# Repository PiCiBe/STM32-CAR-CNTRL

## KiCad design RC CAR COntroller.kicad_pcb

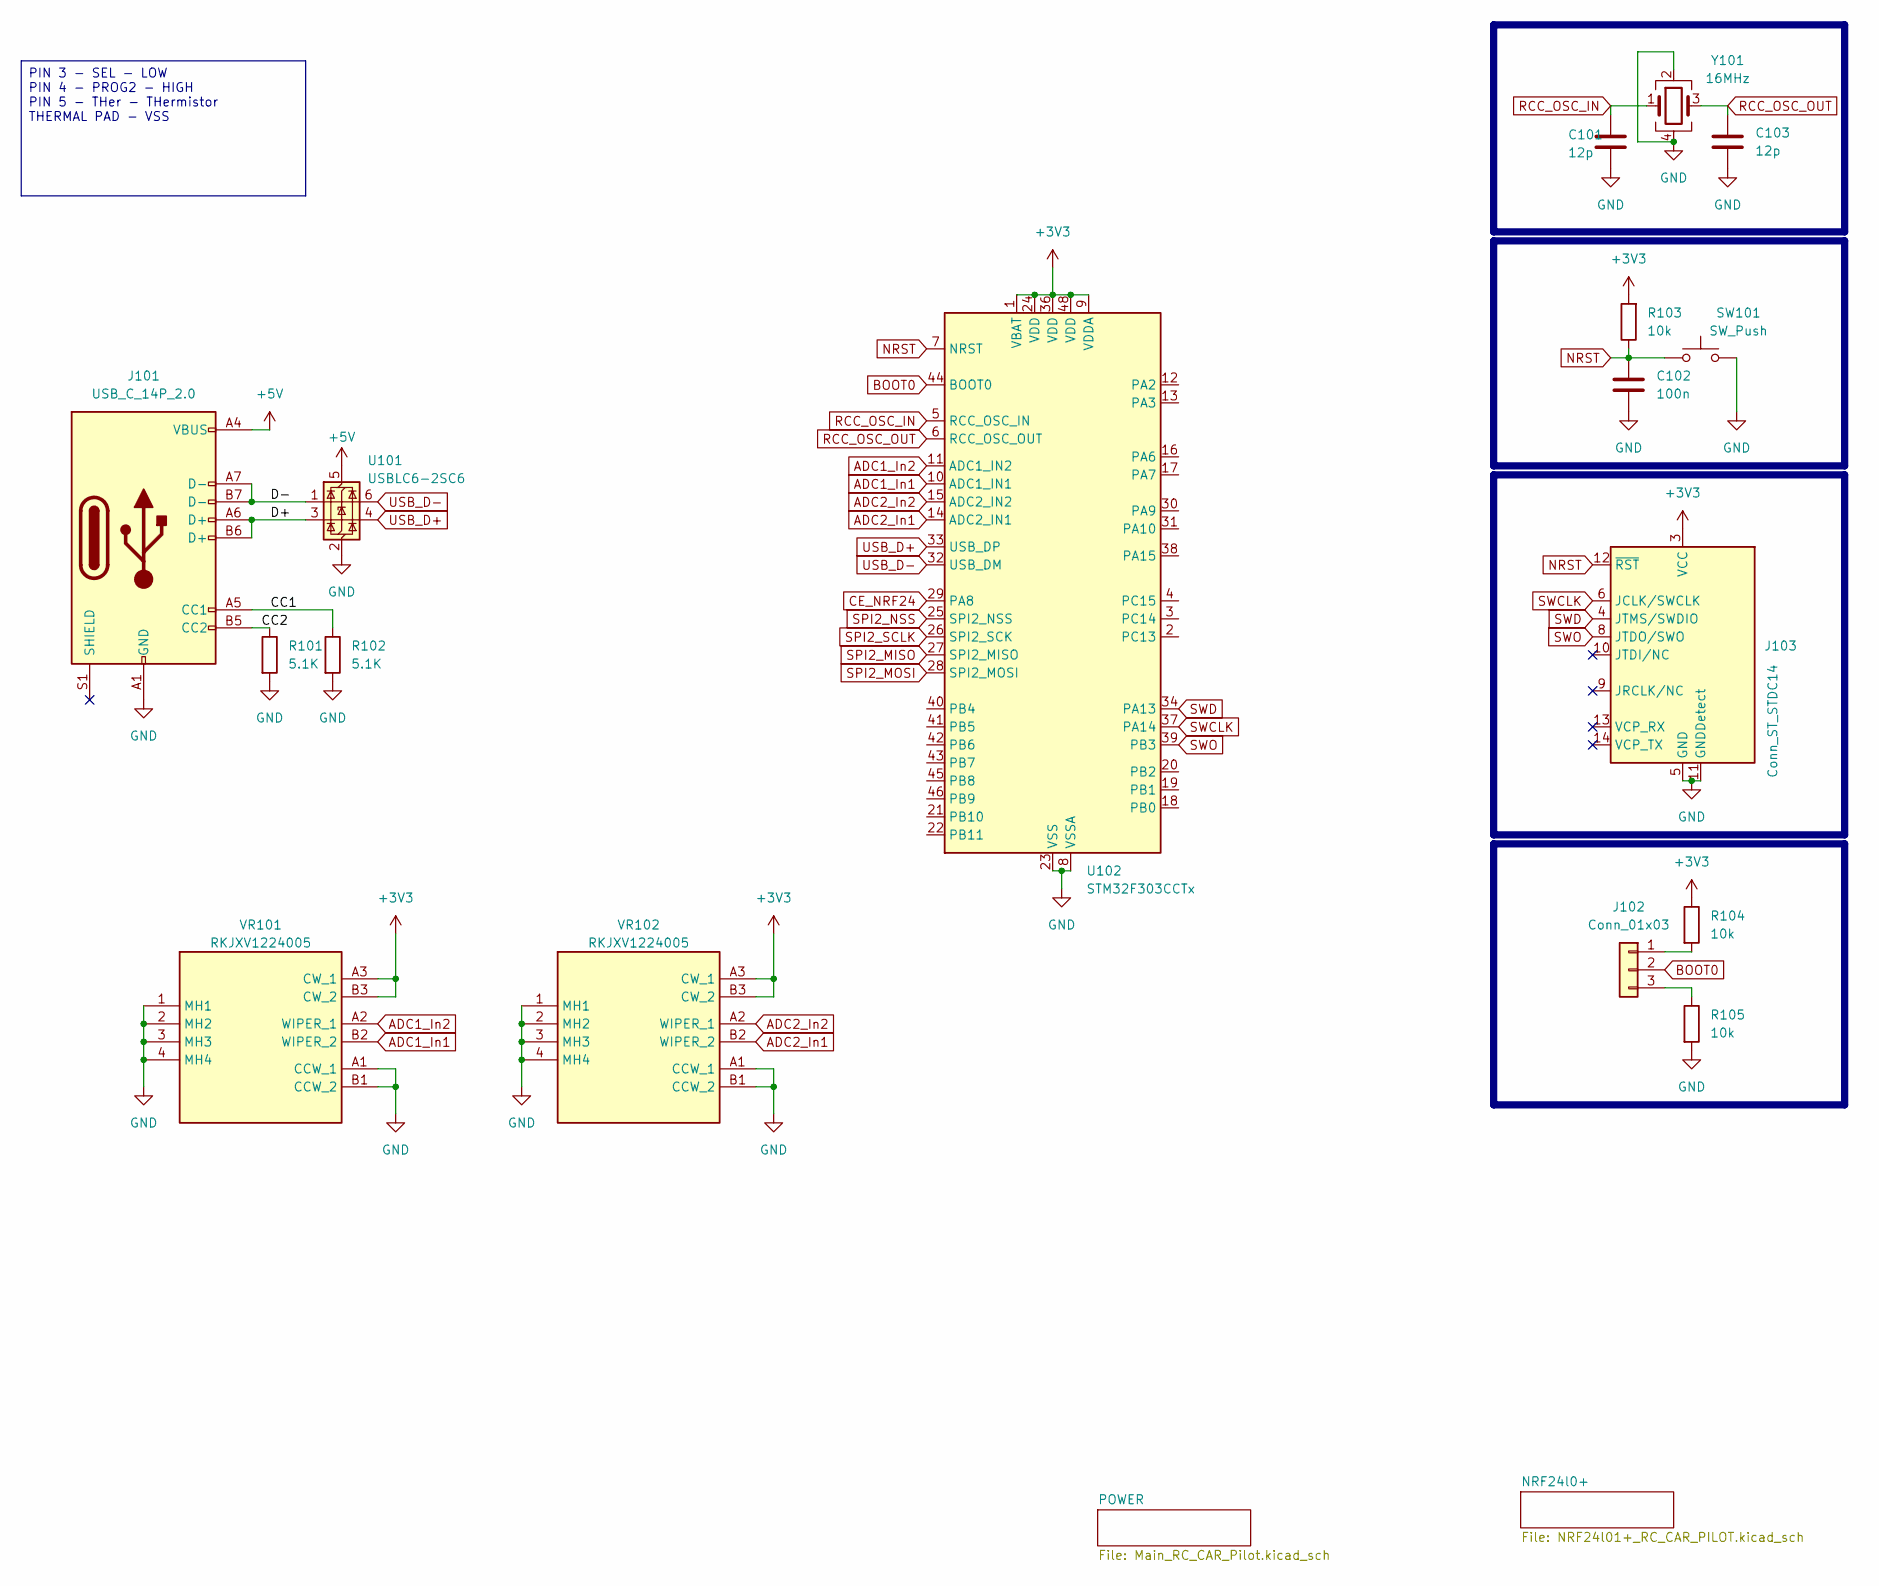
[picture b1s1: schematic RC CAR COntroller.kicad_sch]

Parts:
C101: 12p; C_0402_1005Metric_Pad0.74x0.62mm_HandSolder; lcsc C326662
C102: 100n; C_0603_1608Metric; LCSC C14663
C103: 12p; C_0402_1005Metric_Pad0.74x0.62mm_HandSolder; LCSC C326662
J101: USB_C_14P_2.0; USB_C_Receptacle_G-Switch_GT-USB-7010ASV
J102: Conn_01x03; PinHeader_1x03_P2.54mm_Vertical_SMD_Pin1Left; LCSC C19192025
J103: Conn_ST_STDC14; PinHeader_2x07_P1.27mm_Vertical_SMD
R101, R102: 5.1K; R_0603_1608Metric; LCSC C2907044
R103: 10k; R_0603_1608Metric; lcsc C98220
R104, R105: 10k; R_0603_1608Metric; LCSC C98220
SW101: SW_Push; SW_PUSH_6mm
U101: USBLC6-2SC6; SOT-23-6; LCSC C81523
U102: STM32F303CCTx; LQFP-48_7x7mm_P0.5mm
VR101, VR102: RKJXV1224005; Manufacturer_Part_Number RKJXV1224005; Mouser Part Number 688-RKJXV1224005
Y101: 16MHz; TSX3225160000MF18XAC0; LCSC C1986974

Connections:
+3V3: J103.3 (VCC), R103.2, R104.1, U102.1 (VBAT), U102.9 (VDDA), U102.24 (VDD), U102.36 (VDD), U102.48 (VDD), VR101.A3 (CW_1), VR101.B3 (CW_2), VR102.A3 (CW_1), VR102.B3 (CW_2); also elsewhere on the board
+5V: J101.A4 (VBUS), J101.A9 (VBUS), J101.B4 (VBUS), J101.B9 (VBUS), U101.5 (VBUS); also elsewhere on the board
/D+: J101.A6 (D+), J101.B6 (D+), U101.3 (I/O2)
/D-: J101.A7 (D-), J101.B7 (D-), U101.1 (I/O1)
ADC1_In1: U102.10 (ADC1_IN1), VR101.B2 (WIPER_2)
ADC1_In2: U102.11 (ADC1_IN2), VR101.A2 (WIPER_1)
ADC2_In1: U102.14 (ADC2_IN1), VR102.B2 (WIPER_2)
ADC2_In2: U102.15 (ADC2_IN2), VR102.A2 (WIPER_1)
BOOT0: J102.2, U102.44 (BOOT0)
CE_NRF24: U102.29 (PA8); also elsewhere on the board
GND: C101.2, C102.2, C103.2, J101.A1 (GND), J101.A12 (GND), J101.B1 (GND), J101.B12 (GND), J103.5 (GND), J103.7 (GND), J103.11 (GNDDetect), R101.2, R102.2, R105.2, SW101.2, U101.2 (GND), U102.8 (VSSA), U102.23 (VSS), U102.35 (VSS), U102.47 (VSS), VR101.1 (MH1), VR101.2 (MH2), VR101.3 (MH3), VR101.4 (MH4), VR101.A1 (CCW_1), VR101.B1 (CCW_2), VR102.1 (MH1), VR102.2 (MH2), VR102.3 (MH3), VR102.4 (MH4), VR102.A1 (CCW_1), VR102.B1 (CCW_2), Y101.2, Y101.4; also elsewhere on the board
NRST: C102.1, J103.12 (~RST), R103.1, SW101.1, U102.7 (NRST)
unnamed: J101.A5 (CC1), R102.1
unnamed: J101.B5 (CC2), R101.1
unnamed: J102.1, R104.2
unnamed: J102.3, R105.1
RCC_OSC_IN: C101.1, U102.5 (RCC_OSC_IN), Y101.1
RCC_OSC_OUT: C103.1, U102.6 (RCC_OSC_OUT), Y101.3
SPI2_MISO: U102.27 (SPI2_MISO); also elsewhere on the board
SPI2_MOSI: U102.28 (SPI2_MOSI); also elsewhere on the board
SPI2_NSS: U102.25 (SPI2_NSS); also elsewhere on the board
SPI2_SCLK: U102.26 (SPI2_SCK); also elsewhere on the board
SWCLK: J103.6 (JCLK/SWCLK), U102.37 (PA14)
SWD: J103.4 (JTMS/SWDIO), U102.34 (PA13)
SWO: J103.8 (JTDO/SWO), U102.39 (PB3)
USB_D+: U101.4 (I/O2), U102.33 (USB_DP)
USB_D-: U101.6 (I/O1), U102.32 (USB_DM)

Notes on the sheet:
PIN 3 - SEL - LOW PIN 4 - PROG2 - HIGH PIN 5 - THer - THermistor THERMAL PAD - VSS

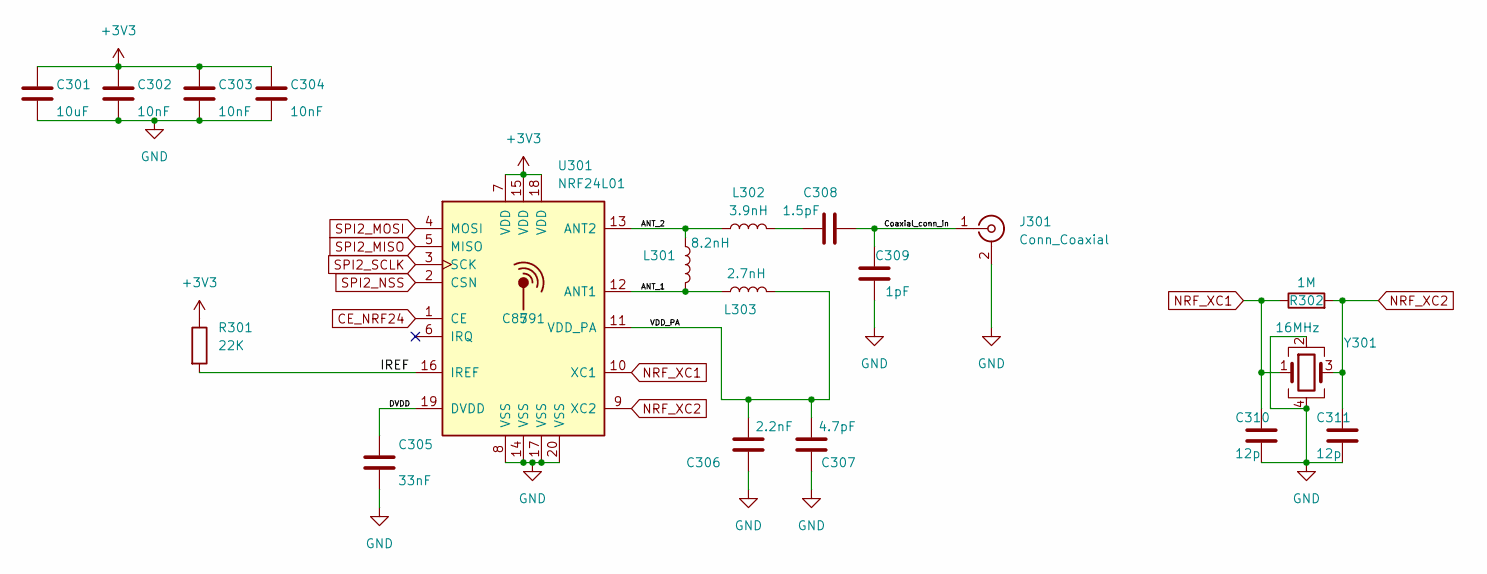
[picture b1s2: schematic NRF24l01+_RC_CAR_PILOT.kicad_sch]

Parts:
C301: 10uF; C_0603_1608Metric_Pad1.08x0.95mm_HandSolder; LCSC C2959727
C302: 10nF; C_0402_1005Metric_Pad0.74x0.62mm_HandSolder; LCSC C60133
C303, C304: 10nF; C_0402_1005Metric_Pad0.74x0.62mm_HandSolder; LCSC part number C60133
C305: 33nF; C_0402_1005Metric_Pad0.74x0.62mm_HandSolder; LCSC C301939
C306: 2.2nF; C_0402_1005Metric_Pad0.74x0.62mm_HandSolder; LCSC C7393866
C307: 4.7pF; C_0402_1005Metric_Pad0.74x0.62mm_HandSolder; LCSC C2915773
C308: 1.5pF; C_0402_1005Metric_Pad0.74x0.62mm_HandSolder; LCSC C189471
C309: 1pF; C_0402_1005Metric_Pad0.74x0.62mm_HandSolder; LCSC C309455
C310: 12p; C_0402_1005Metric_Pad0.74x0.62mm_HandSolder; LCSC C1547
C311: 12p; C_0402_1005Metric_Pad0.74x0.62mm_HandSolder; LCSC part number C1547
J301: Conn_Coaxial; SMA_Amphenol_132134-11_Vertical; LCSC C496550
L301: 8.2nH; L_0402_1005Metric; LCSC C7427065
L302: 3.9nH; L_0402_1005Metric; LCSC C6807988
L303: 2.7nH; L_0402_1005Metric; LCSC C434826
R301: 22K; R_0402_1005Metric_Pad0.72x0.64mm_HandSolder; LCSC C82868
R302: 1M; R_0402_1005Metric_Pad0.72x0.64mm_HandSolder; LCSC C93949
U301: NRF24L01; QFN-20-1EP_4x4mm_P0.5mm_EP2.5x2.5mm; LCSC C8791
Y301: 16MHz; Crystal_SMD_3225-4Pin_3.2x2.5mm; LCSC C13738

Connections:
+3V3: C301.1, C302.1, C303.1, C304.1, R301.1, U301.7 (VDD), U301.15 (VDD), U301.18 (VDD); also elsewhere on the board
/NRF24l0+/ANT_1: L301.1, L303.2, U301.12 (ANT1)
/NRF24l0+/ANT_2: L301.2, L302.1, U301.13 (ANT2)
/NRF24l0+/Coaxial_conn_in: C308.2, C309.2, J301.1 (In)
/NRF24l0+/DVDD: C305.1, U301.19 (DVDD)
/NRF24l0+/VDD_PA: C306.2, C307.2, L303.1, U301.11 (VDD_PA)
CE_NRF24: U301.1 (CE); also elsewhere on the board
GND: C301.2, C302.2, C303.2, C304.2, C305.2, C306.1, C307.1, C309.1, C310.2, C311.2, J301.2 (Ext), U301.8 (VSS), U301.14 (VSS), U301.17 (VSS), U301.20 (VSS), Y301.2, Y301.4; also elsewhere on the board
NRF_XC1: C310.1, R302.1, U301.10 (XC1), Y301.1
NRF_XC2: C311.1, R302.2, U301.9 (XC2), Y301.3
unnamed: C308.1, L302.2
unnamed: R301.2, U301.16 (IREF)
SPI2_MISO: U301.5 (MISO); also elsewhere on the board
SPI2_MOSI: U301.4 (MOSI); also elsewhere on the board
SPI2_NSS: U301.2 (CSN); also elsewhere on the board
SPI2_SCLK: U301.3 (SCK); also elsewhere on the board

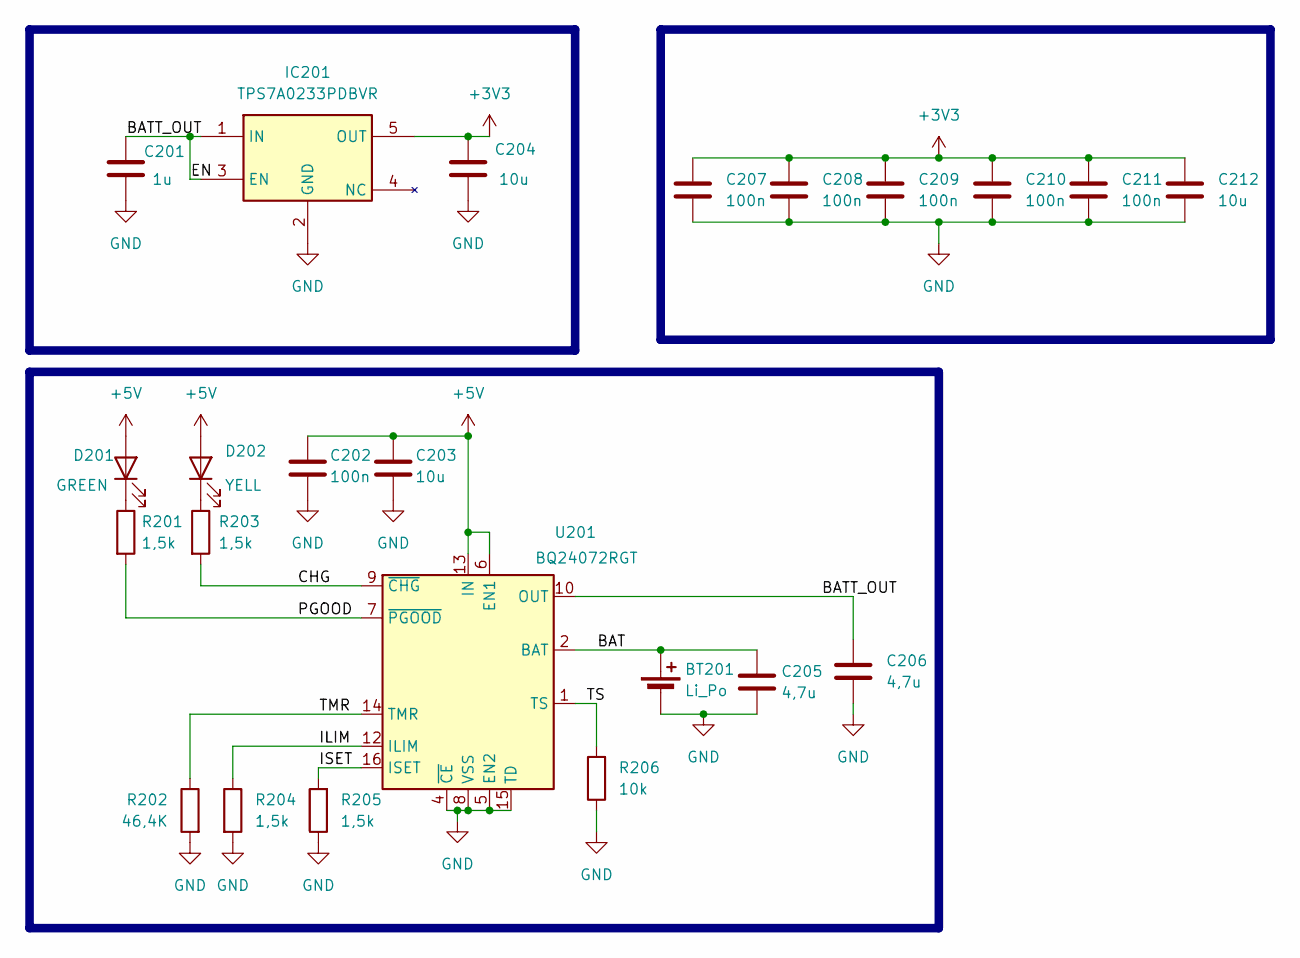
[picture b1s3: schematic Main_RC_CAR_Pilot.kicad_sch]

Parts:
BT201: Li_Po; 532610271; LCSC C177225
C201: 1u; C_0805_2012Metric; lcsc C28323
C202, C207, C208, C209, C210, C211: 100n; C_0603_1608Metric; lcsc C14663
C203, C204, C212: 10u; C_0805_2012Metric; LCSC C15850
C205, C206: 4,7u; C_0805_2012Metric; LCSC C98192
D201: GREEN; LED_0603_1608Metric; LCSC C19171301
D202: YELL; LED_0603_1608Metric; LCSC C965800
IC201: TPS7A0233PDBVR; SOT95P280X145-5N; Manufacturer_Part_Number TPS7A0233PDBVR; Mouser Part Number 595-TPS7A0233PDBVR
R201, R203, R204, R205: 1,5k; R_0603_1608Metric; LCSC C22843
R202: 46,4K; R_0603_1608Metric; LCSC C3013203
R206: 10k; R_0603_1608Metric; LCSC C98220
U201: BQ24072RGT; VQFN-16-1EP_3x3mm_P0.5mm_EP1.6x1.6mm; LCSC C140288

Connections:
+3V3: C204.1, C207.1, C208.1, C209.1, C210.1, C211.1, C212.1, IC201.5 (OUT); also elsewhere on the board
+5V: C202.1, C203.1, D201.2 (A), D202.2 (A), U201.6 (EN1), U201.13 (IN); also elsewhere on the board
/POWER/BAT: BT201.1 (+), C205.1, U201.2 (BAT), U201.3 (BAT)
/POWER/BATT_OUT: C201.1, C206.1, IC201.1 (IN), IC201.3 (EN), U201.10 (OUT), U201.11 (OUT)
/POWER/CHG: R203.2, U201.9 (~CHG)
/POWER/ILIM: R204.1, U201.12 (ILIM)
/POWER/ISET: R205.2, U201.16 (ISET)
/POWER/PGOOD: R201.2, U201.7 (~PGOOD)
/POWER/TMR: R202.1, U201.14 (TMR)
/POWER/TS: R206.2, U201.1 (TS)
GND: BT201.2 (-), C201.2, C202.2, C203.2, C204.2, C205.2, C206.2, C207.2, C208.2, C209.2, C210.2, C211.2, C212.2, IC201.2 (GND), R202.2, R204.2, R205.1, R206.1, U201.4 (~CE), U201.5 (EN2), U201.8 (VSS), U201.15 (TD), U201.17 (VSS); also elsewhere on the board
unnamed: D201.1 (K), R201.1
unnamed: D202.1 (K), R203.1

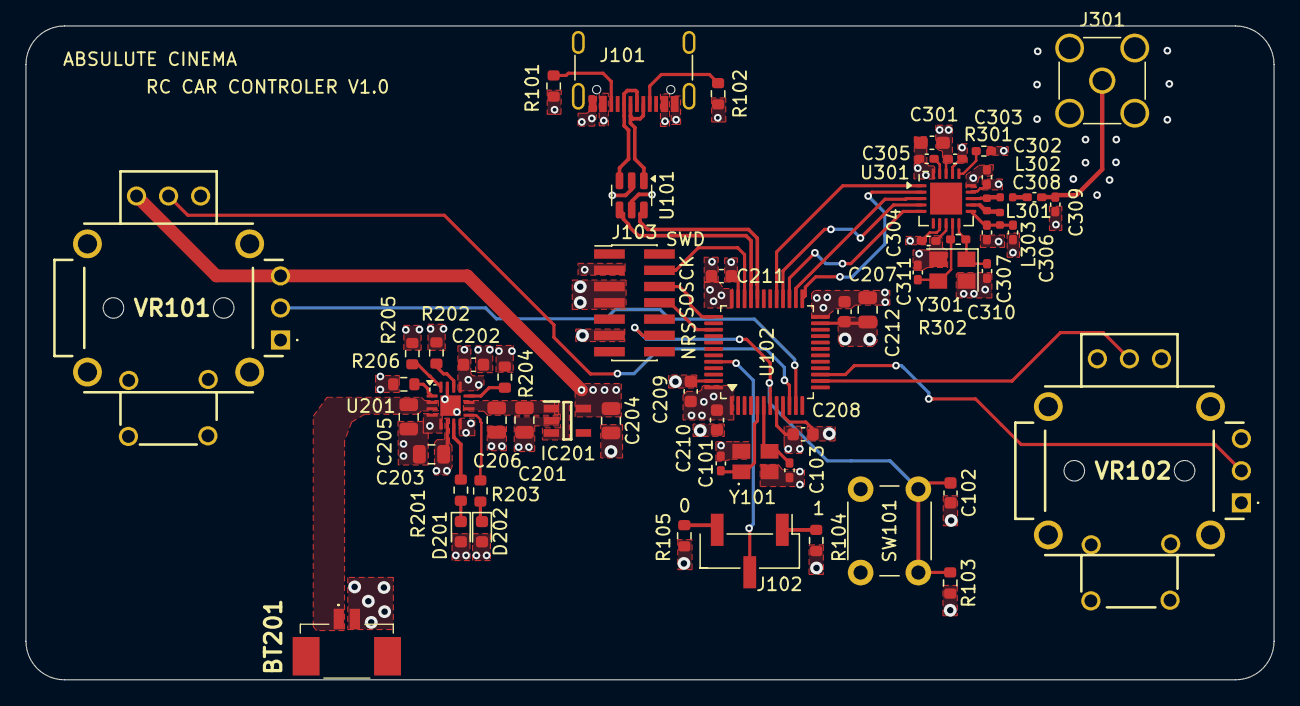
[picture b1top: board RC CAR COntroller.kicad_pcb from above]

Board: 4 copper layers, 97.3 x 51.0 mm, 59 parts (0 on the bottom side), 46 nets.

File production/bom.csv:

Designator,Footprint,Quantity,Value,LCSC Part #
BT201,532610271,1,Li_Po,C177225
"C101, C311",0402,2,12p,
C102,0603,1,100n,C14663
C103,0402,1,12p,C326662
C201,0805,1,1u,
"C202, C207, C208, C209, C210, C211",0603,6,100n,
"C203, C204, C212",0805,3,10u,C15850
"C205, C206",0805,2,"4,7u",C98192
C301,0603,1,10uF,C2959727
C302,0402,1,10nF,C60133
"C303, C304",0402,2,10nF,
C305,0402,1,33nF,C301939
C306,0402,1,2.2nF,C7393866
C307,0402,1,4.7pF,C2915773
C308,0402,1,1.5pF,C189471
C309,0402,1,1pF,C309455
C310,0402,1,12p,C1547
D201,0603,1,GREEN,C19171301
D202,0603,1,YELL,C965800
IC201,SOT95P280X145-5N,1,TPS7A0233PDBVR,
J101,USB_C_Receptacle_G-Switch_GT-USB-7010ASV,1,USB_C_14P_2.0,
J102,PinHeader_1x03_P2.54mm_Vertical_SMD_Pin1Left,1,Conn_01x03,C19192025
J103,PinHeader_2x07_P1.27mm_Vertical_SMD,1,Conn_ST_STDC14,
J301,SMA_Amphenol_132134-11_Vertical,1,Conn_Coaxial,C496550
L301,0402,1,8.2nH,C7427065
L302,0402,1,3.9nH,C6807988
L303,0402,1,2.7nH,C434826
"R101, R102",0603,2,5.1K,C2907044
R103,0603,1,10k,
"R104, R105, R206",0603,3,10k,C98220
"R201, R203, R204, R205",0603,4,"1,5k",C22843
R202,0603,1,"46,4K",C3013203
R301,0402,1,22K,C82868
R302,0402,1,1M,C93949
SW101,SW_PUSH_6mm,1,SW_Push,
U101,SOT-23-6,1,USBLC6-2SC6,C81523
U102,LQFP-48_7x7mm_P0.5mm,1,STM32F303CCTx,
U201,VQFN-16-1EP_3x3mm_P0.5mm_EP1.6x1.6mm,1,BQ24072RGT,C140288
U301,QFN-20-1EP_4x4mm_P0.5mm_EP2.5x2.5mm,1,NRF24L01,C8791
"VR101, VR102",RKJXV1224005,2,RKJXV1224005,
Y101,TSX3225160000MF18XAC0,1,16MHz,C1986974
Y301,Crystal_SMD_3225-4Pin_3.2x2.5mm,1,16MHz,C13738

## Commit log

2026-04-06 added resistr test
2026-04-06 added led diode test
2026-04-06 added more led test
